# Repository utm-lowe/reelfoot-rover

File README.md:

# Reelfoot Rover

The Reelfoot Rover is a robot which is used in the CSCI 458 - Autonomous Mobile 
Robotics at the University of Tennessee at Matin. This robot is a 4wd robot 
with each wheel being independantly controlled via PWM. The robot is controlled
via a Raspberry Pi computer, and power for the motors and all peripherals is drawn
from the power rails of the Raspberr Pi.

This repository contains the circuit board which controls the following:
- 4 Independentally Controlled Motors
- 4 Optical Wheel Encoders
- 3 HC-SR04 Ultrasonic Range Finder (Sonars)

The board is designed to be used along with the Raspberry Pi Sense Hat. You don't
need the sense hat, but I rather like it. So I made sure to not use any of the pins 
used by the sense hat. You can stack this board under the sense hat, or connect it
with a ribbon cable.

This board is licensed under the MIT License and provided in the hope that you'll
find it helpful and use it in your own robotics tinkering.

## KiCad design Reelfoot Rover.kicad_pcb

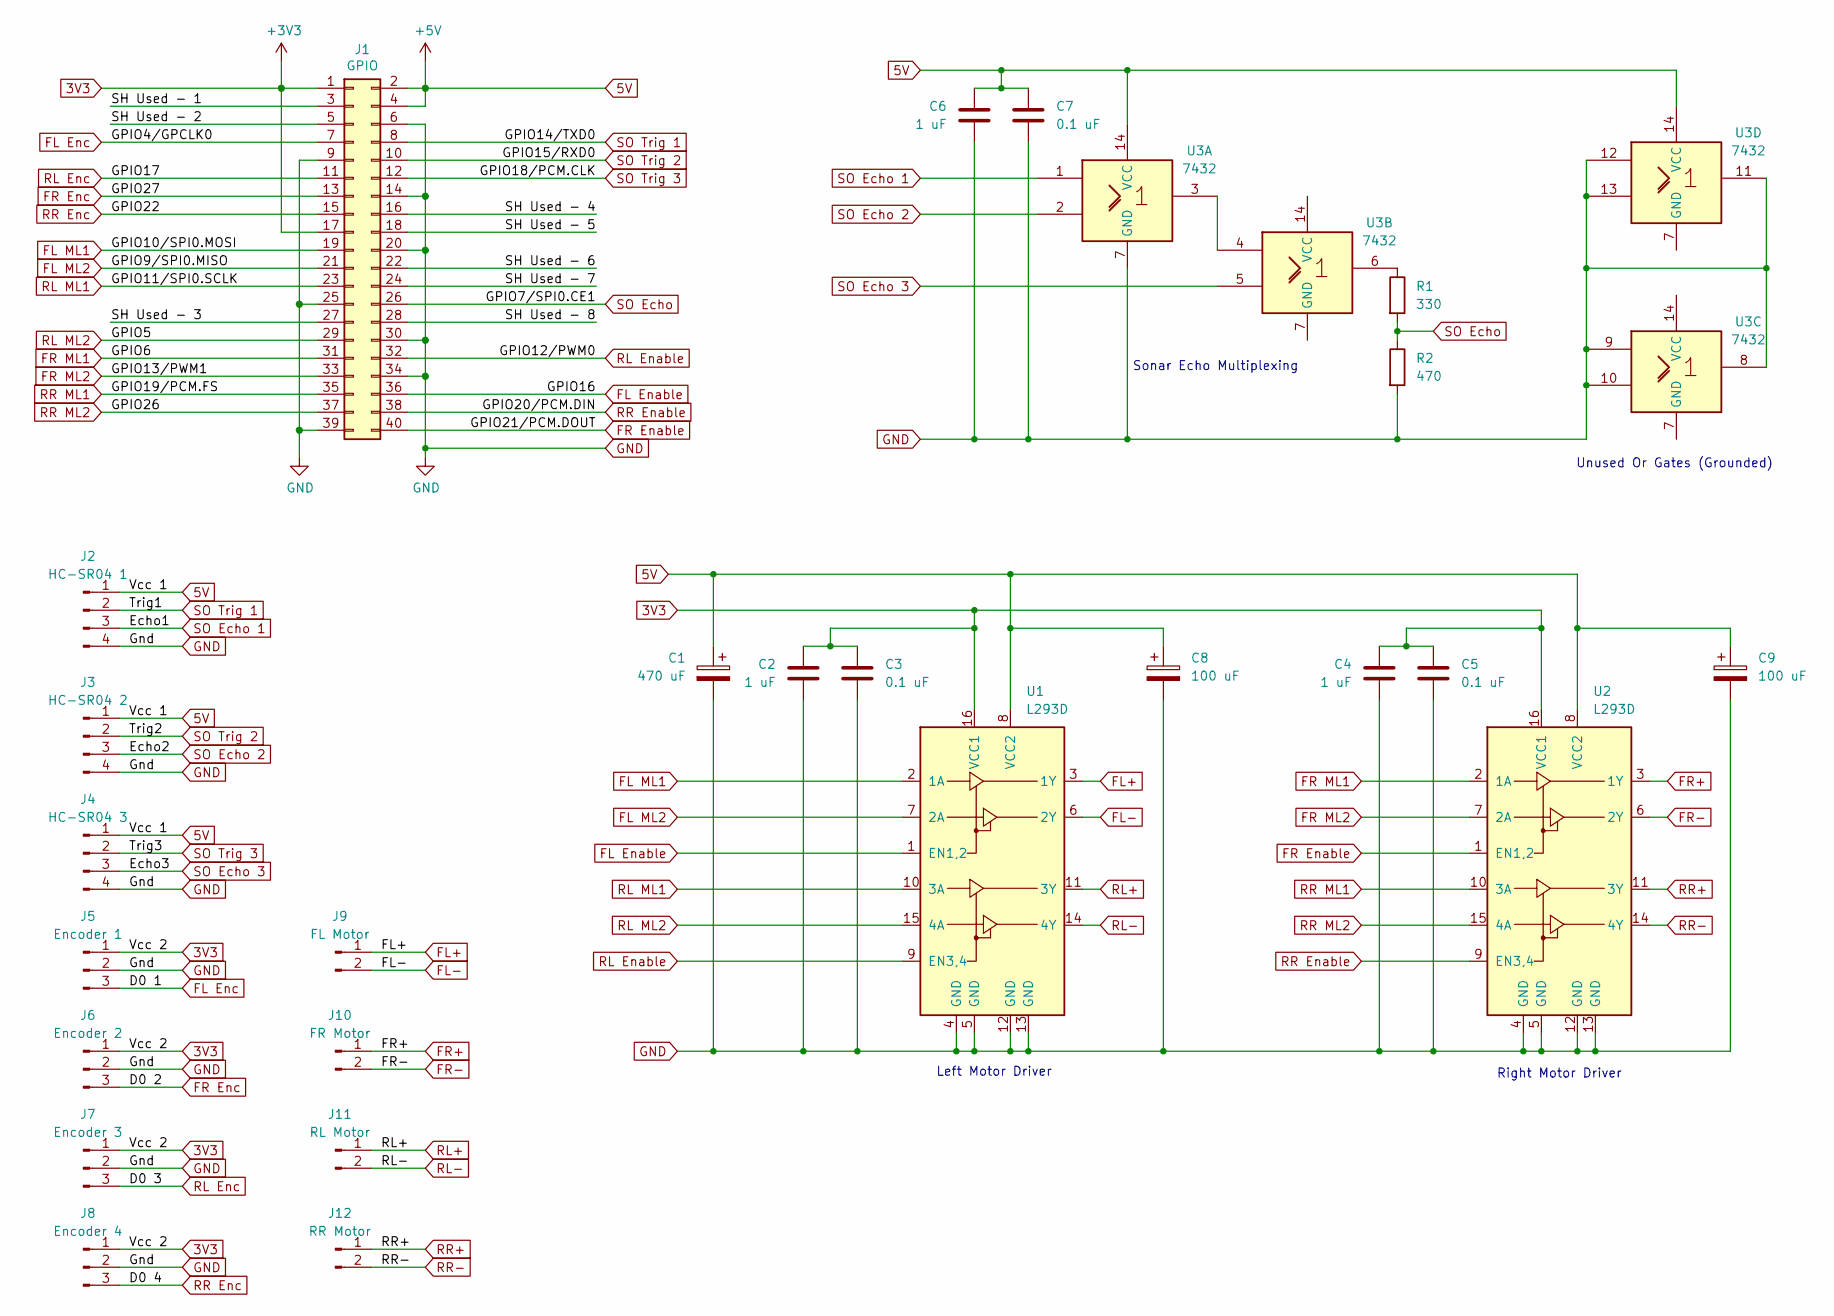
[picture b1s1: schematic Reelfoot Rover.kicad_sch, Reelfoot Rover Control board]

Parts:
C1: 470 uF; CP_Radial_D8.0mm_P2.50mm
C2, C4, C6: 1 uF; C_Disc_D5.0mm_W2.5mm_P5.00mm
C3, C5, C7: 0.1 uF; C_Disc_D5.0mm_W2.5mm_P5.00mm
C8, C9: 100 uF; CP_Radial_D5.0mm_P2.00mm
J1: GPIO; PinSocket_2x20_P2.54mm_Vertical
J2: HC-SR04 1; PinHeader_1x04_P2.54mm_Vertical
J3: HC-SR04 2; PinHeader_1x04_P2.54mm_Vertical
J4: HC-SR04 3; PinHeader_1x04_P2.54mm_Vertical
J5: Encoder 1; PinHeader_1x03_P2.54mm_Vertical
J6: Encoder 2; PinHeader_1x03_P2.54mm_Vertical
J7: Encoder 3; PinHeader_1x03_P2.54mm_Vertical
J8: Encoder 4; PinHeader_1x03_P2.54mm_Vertical
J9: FL Motor; PinHeader_1x02_P2.54mm_Vertical
J10: FR Motor; PinHeader_1x02_P2.54mm_Vertical
J11: RL Motor; PinHeader_1x02_P2.54mm_Vertical
J12: RR Motor; PinHeader_1x02_P2.54mm_Vertical
R1: 330; R_Axial_DIN0207_L6.3mm_D2.5mm_P7.62mm_Horizontal
R2: 470; R_Axial_DIN0207_L6.3mm_D2.5mm_P7.62mm_Horizontal
U1, U2: L293D; DIP-16_W7.62mm
U3: 7432; DIP-14_W7.62mm

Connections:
3V3: C2.1, C3.1, C4.1, C5.1, J1.1, J1.17, J5.1, J6.1, J7.1, J8.1, U1.16 (VCC1), U2.16 (VCC1)
5V: C1.1, C6.1, C7.1, C8.1, C9.1, J1.2, J1.4, J2.1, J3.1, J4.1, U1.8 (VCC2), U2.8 (VCC2), U3.14 (VCC)
/SH Used - 1: J1.3
/SH Used - 2: J1.5
/SH Used - 3: J1.27
/SH Used - 4: J1.16
/SH Used - 5: J1.18
/SH Used - 6: J1.22
/SH Used - 7: J1.24
/SH Used - 8: J1.28
FL Enable: J1.36, U1.1 (EN1,2)
FL Enc: J1.7, J5.3
FL ML1: J1.19, U1.2 (1A)
FL ML2: J1.21, U1.7 (2A)
FL+: J9.1, U1.3 (1Y)
FL-: J9.2, U1.6 (2Y)
FR Enable: J1.40, U2.1 (EN1,2)
FR Enc: J1.13, J6.3
FR ML1: J1.31, U2.2 (1A)
FR ML2: J1.33, U2.7 (2A)
FR+: J10.1, U2.3 (1Y)
FR-: J10.2, U2.6 (2Y)
GND: C1.2, C2.2, C3.2, C4.2, C5.2, C6.2, C7.2, C8.2, C9.2, J1.6, J1.9, J1.14, J1.20, J1.25, J1.30, J1.34, J1.39, J2.4, J3.4, J4.4, J5.2, J6.2, J7.2, J8.2, R2.2, U1.4 (GND), U1.5 (GND), U1.12 (GND), U1.13 (GND), U2.4 (GND), U2.5 (GND), U2.12 (GND), U2.13 (GND), U3.7 (GND), U3.8, U3.9, U3.10, U3.11, U3.12, U3.13
unnamed: R1.1, U3.6
unnamed: U3.3, U3.4
RL Enable: J1.32, U1.9 (EN3,4)
RL Enc: J1.11, J7.3
RL ML1: J1.23, U1.10 (3A)
RL ML2: J1.29, U1.15 (4A)
RL+: J11.1, U1.11 (3Y)
RL-: J11.2, U1.14 (4Y)
RR Enable: J1.38, U2.9 (EN3,4)
RR Enc: J1.15, J8.3
RR ML1: J1.35, U2.10 (3A)
RR ML2: J1.37, U2.15 (4A)
RR+: J12.1, U2.11 (3Y)
RR-: J12.2, U2.14 (4Y)
SO Echo: J1.26, R1.2, R2.1
SO Echo 1: J2.3, U3.1
SO Echo 2: J3.3, U3.2
SO Echo 3: J4.3, U3.5
SO Trig 1: J1.8, J2.2
SO Trig 2: J1.10, J3.2
SO Trig 3: J1.12, J4.2

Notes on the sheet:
Unused Or Gates (Grounded)
Right Motor Driver
Sonar Echo Multiplexing
Left Motor Driver

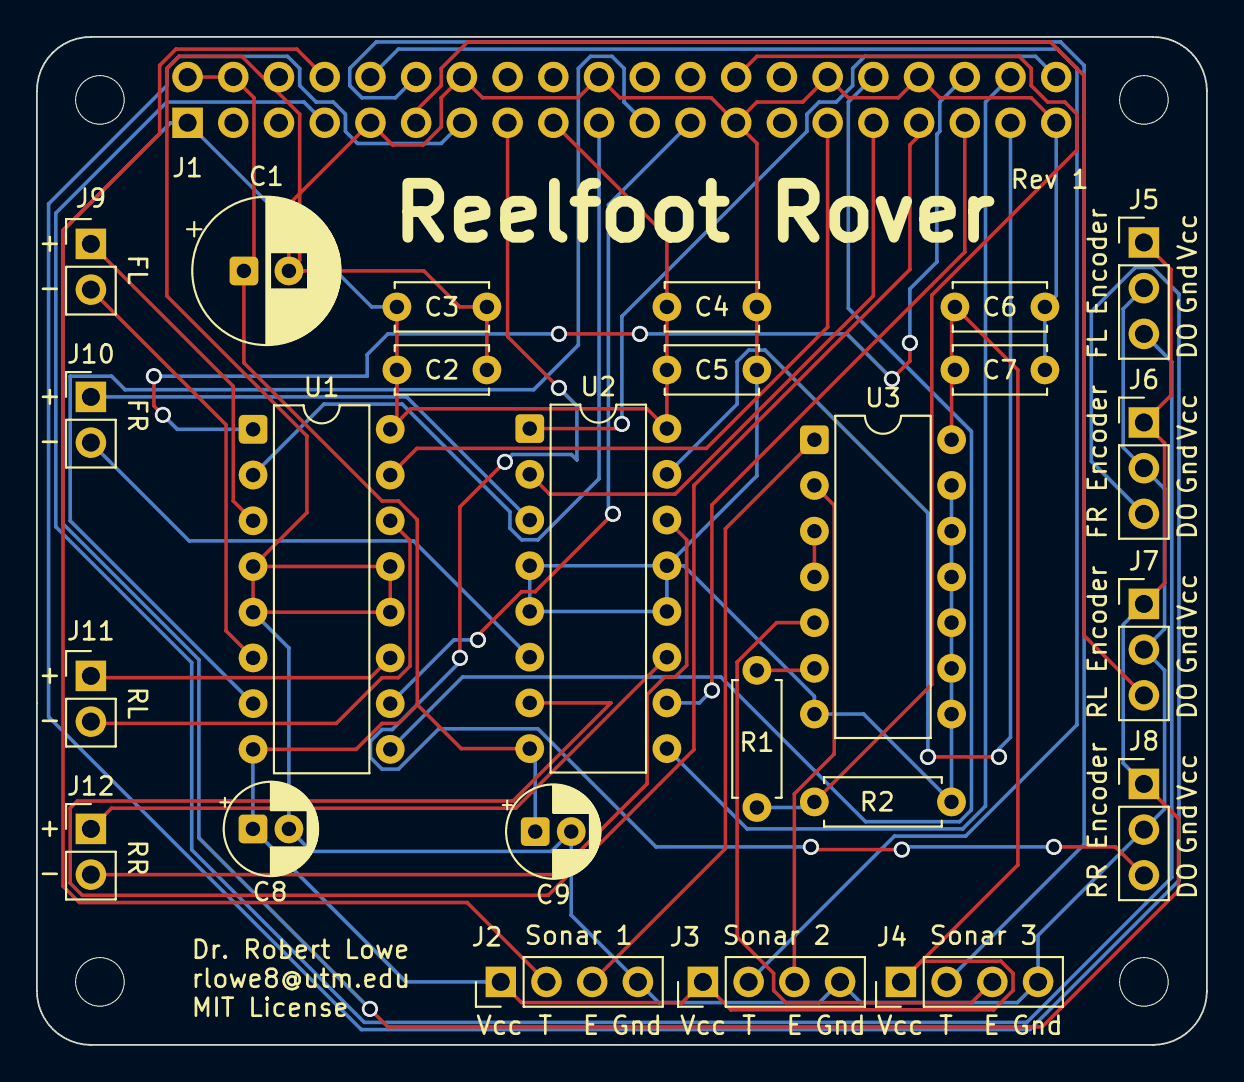
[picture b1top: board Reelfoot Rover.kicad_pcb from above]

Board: 2 copper layers, 65.0 x 56.0 mm, 30 parts (1 on the bottom side), 36 nets.

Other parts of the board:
MH1, MH2, MH3, MH4: MountingHole_2.7mm_M2.5
